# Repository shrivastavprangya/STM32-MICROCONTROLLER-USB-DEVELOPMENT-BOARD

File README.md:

# STM32 Microcontroller USB Development Board

This project is a custom STM32 microcontroller based USB development board designed using KiCad.  
The board includes LDO based 3.3V power regulation, USB interface for communication and power, 
external crystal oscillator for stable clock operation and GPIO expansion headers.

The PCB is designed as a 2-layer board with a dedicated ground plane for improved signal integrity 
and stable power distribution.

---

## Features

- STM32 microcontroller based development board
- USB interface for programming and communication
- 3.3V LDO voltage regulator
- External crystal oscillator for accurate clock
- Decoupling capacitors for power stability
- GPIO expansion headers
- 2-layer PCB with ground plane

---

## Design Workflow

Schematic Design  
↓  
Component Selection  
↓  
PCB Layout and Routing  
↓  
Design Rule Check (DRC)  
↓  
Gerber File Generation  
↓  
PCB Manufacturing

---

## PCB Preview

### Schematic

### PCB Layout

### 3D View (Top)

### 3D View (Bottom)

---

## Project Files

- **Schematic** – KiCad schematic design files  
- **PCB Layout** – Complete PCB layout and routing files  
- **Gerber Files** – Manufacturing files used for PCB fabrication 

---

## Tools Used

- KiCad

---
## Project Structure

STM32-MICROCONTROLLER-USB-DEVELOPMENT-BOARD

│
├── Schematic
│   └── stm32_usb_board.kicad_sch
│
├── PCB
│   └── stm32_usb_board.kicad_pcb
│
├── Gerber
│   └── gerber_files.zip
│
├── Images
│   ├── pcb_top.png
│   ├── pcb_bottom.png
│   └── pcb_3d.png
│
└── README.md

## Author

**Pragya Shrivastav**  
Electronics & Communication Engineer  
PCB Design | Embedded Hardware

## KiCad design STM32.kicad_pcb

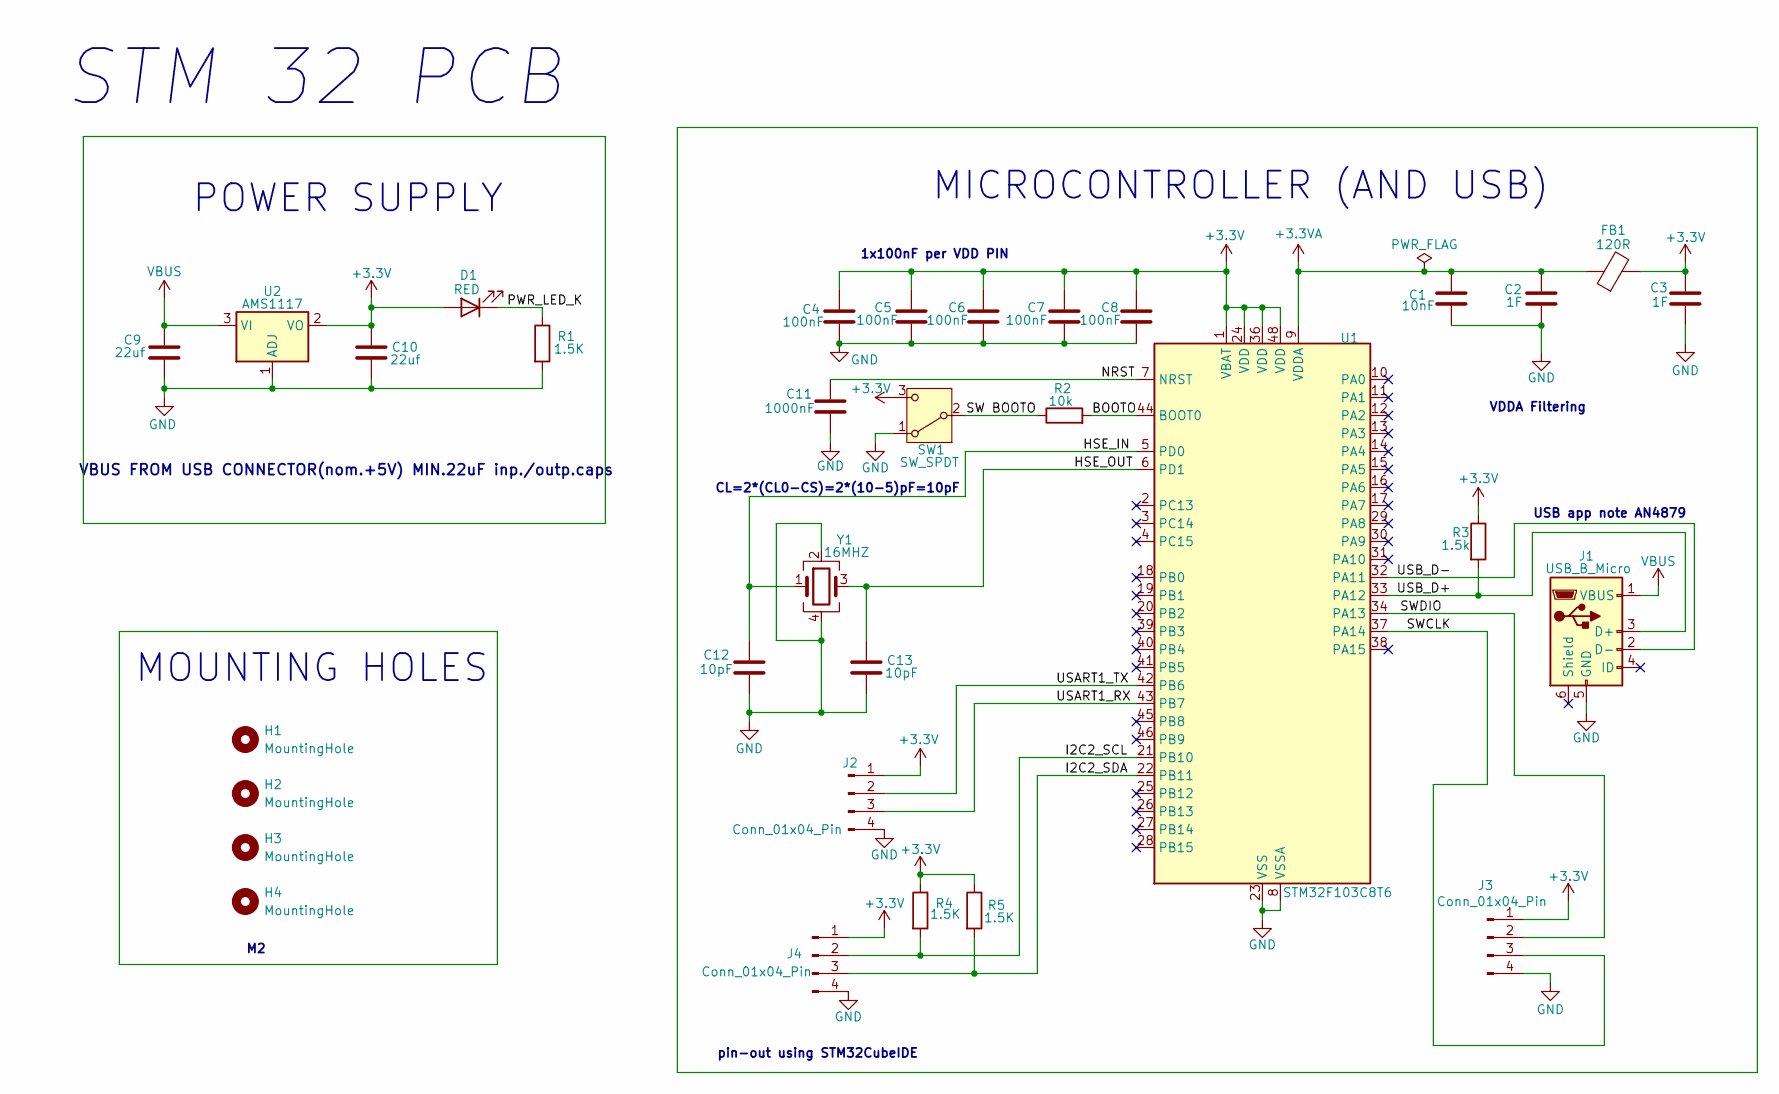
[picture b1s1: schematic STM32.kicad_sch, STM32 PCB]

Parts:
C1: 10nF; C_0402_1005Metric
C2, C3: 1F; C_0402_1005Metric
C4, C5, C6, C7, C8: 100nF; C_0603_1608Metric
C9, C10: 22uf; C_0805_2012Metric
C11: 1000nF; C_0402_1005Metric
C12, C13: 10pF; C_0402_1005Metric
D1: RED; LED_0603_1608Metric
FB1: 120R; L_0603_1608Metric
H1, H2, H3, H4: MountingHole; MountingHole_2.1mm
J1: USB_B_Micro; USB_Micro-B_Wuerth_629105150521
J2, J3, J4: Conn_01x04_Pin; PinHeader_1x04_P2.54mm_Vertical
R1, R4, R5: 1.5K; R_0402_1005Metric
R2: 10k; R_0402_1005Metric
R3: 1.5k; R_0402_1005Metric
SW1: SW_SPDT; SW_E-Switch_EG1224_SPDT_Angled
U1: STM32F103C8T6; LQFP-48_7x7mm_P0.5mm
U2: AMS1117; SOT-223-3_TabPin2
Y1: 16MHZ; Crystal_SMD_3225-4Pin_3.2x2.5mm

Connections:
+3.3V: C3.1, C4.1, C5.1, C6.1, C7.1, C8.1, C10.1, D1.2 (A), FB1.2, J2.1, J3.1, J4.1, R3.1, R4.1, R5.1, SW1.3 (C), U1.1 (VBAT), U1.24 (VDD), U1.36 (VDD), U1.48 (VDD), U2.2 (VO)
+3.3VA: C1.1, C2.1, FB1.1, U1.9 (VDDA)
/BOOTO: R2.2, U1.44 (BOOT0)
/HSE_IN: C12.1, U1.5 (PD0), Y1.1
/HSE_OUT: C13.1, U1.6 (PD1), Y1.3
/I2C2_SCL: J4.2, R4.2, U1.21 (PB10)
/I2C2_SDA: J4.3, R5.2, U1.22 (PB11)
/NRST: C11.1, U1.7 (NRST)
/PWR_LED_K: D1.1 (K), R1.1
/SW BOOTO: R2.1, SW1.2 (B)
/SWCLK: J3.3, U1.37 (PA14)
/SWDIO: J3.2, U1.34 (PA13)
/USART1_RX: J2.3, U1.43 (PB7)
/USART1_TX: J2.2, U1.42 (PB6)
/USB_D+: J1.3 (D+), R3.2, U1.33 (PA12)
/USB_D-: J1.2 (D-), U1.32 (PA11)
GND: C1.2, C2.2, C3.2, C4.2, C5.2, C6.2, C7.2, C8.2, C9.2, C10.2, C11.2, C12.2, C13.2, J1.5 (GND), J2.4, J3.4, J4.4, R1.2, SW1.1 (A), U1.8 (VSSA), U1.23 (VSS), U1.35 (VSS), U1.47 (VSS), U2.1 (ADJ), Y1.2, Y1.4
VBUS: C9.1, J1.1 (VBUS), U2.3 (VI)

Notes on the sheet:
POWER SUPPLY
1x100nF per VDD PIN
USB app note AN4879
VBUS FROM USB CONNECTOR(nom.+5V) MIN.22uF inp./outp.caps
MOUNTING HOLES
CL=2*(CL0-CS)=2*(10-5)pF=10pF
pin-out using STM32CubeIDE
VDDA Filtering
MICROCONTROLLER (AND USB)
STM 32 PCB

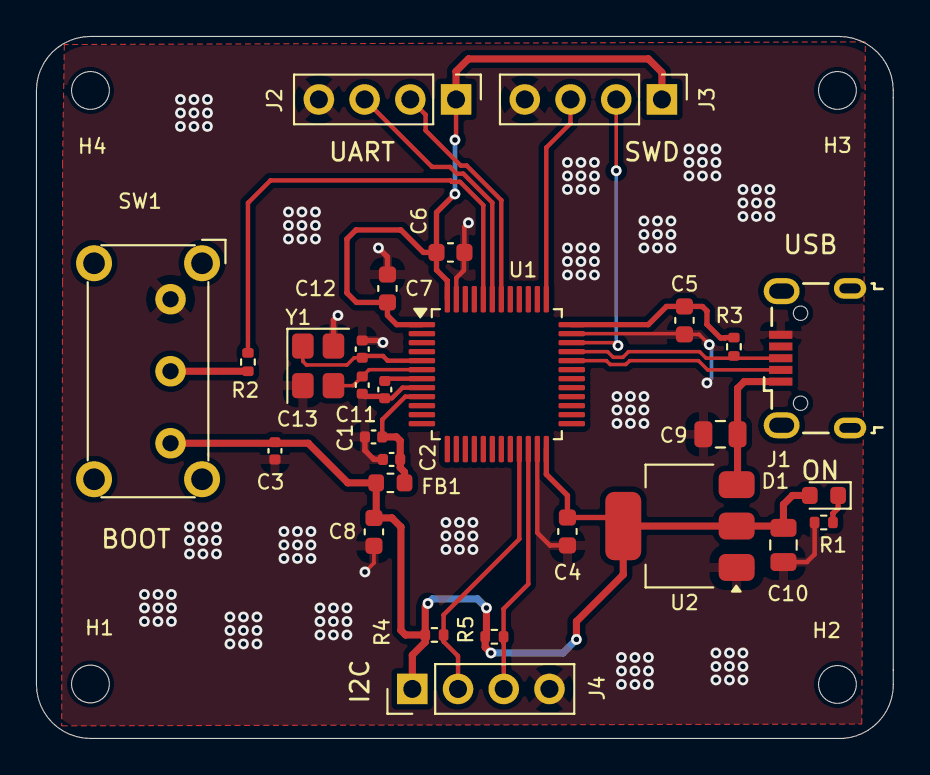
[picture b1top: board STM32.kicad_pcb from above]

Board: 2 copper layers, 47.6 x 39.0 mm, 32 parts (0 on the bottom side), 18 nets.

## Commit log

2026-03-16 Add files via upload
    Initial commit – STM32 USB development board schematic, PCB layout and Gerber files
